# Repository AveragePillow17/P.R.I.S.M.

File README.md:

# P.R.I.S.M.
Portable Radio Instrument for Signal Monitoring

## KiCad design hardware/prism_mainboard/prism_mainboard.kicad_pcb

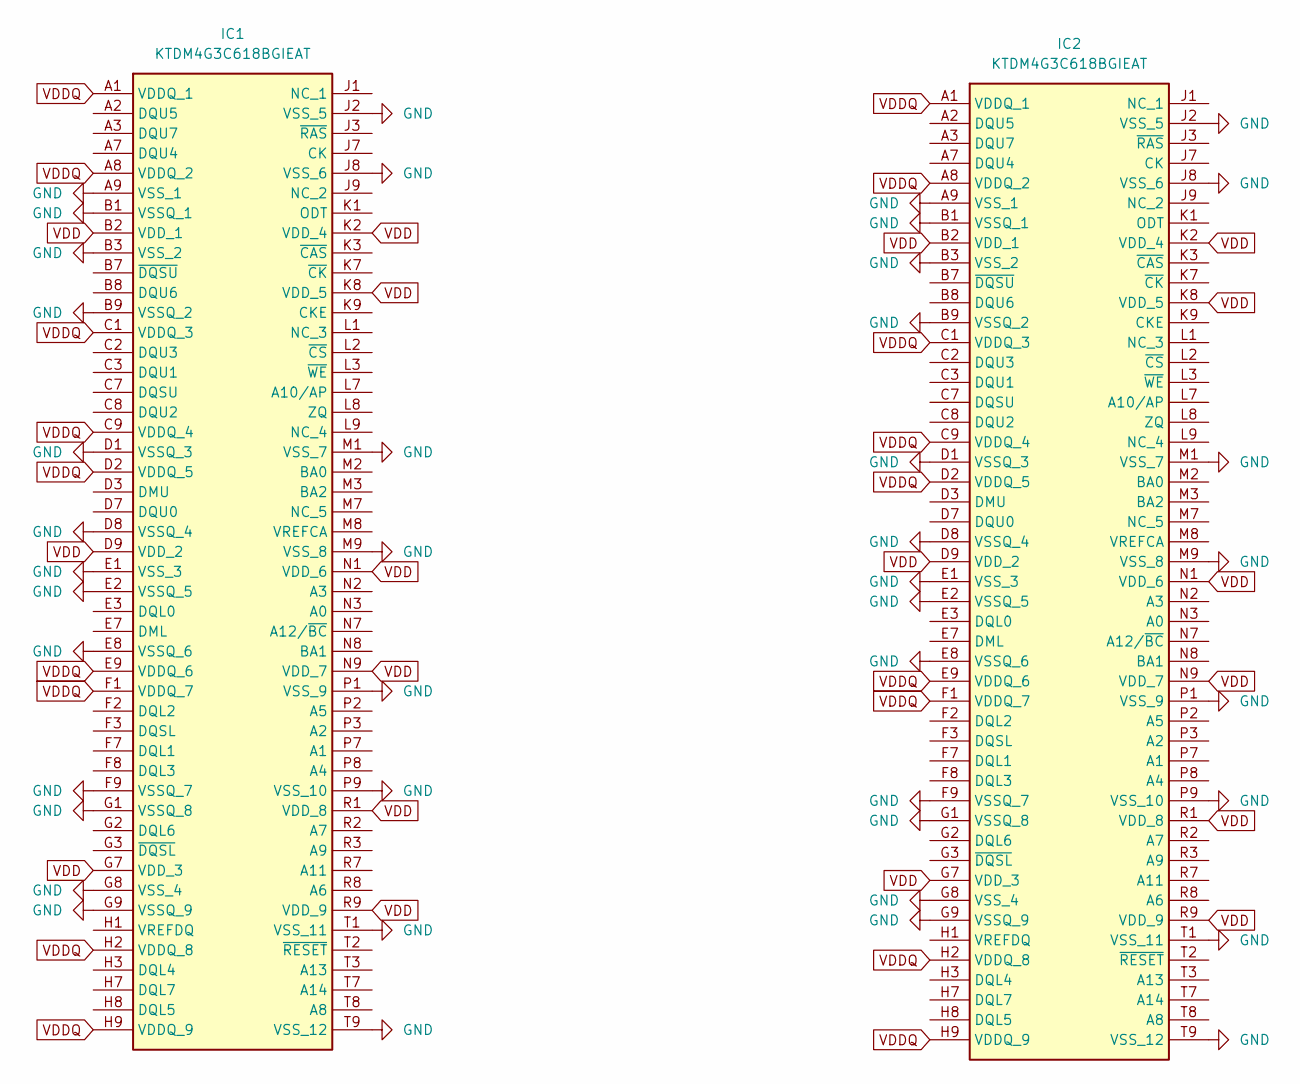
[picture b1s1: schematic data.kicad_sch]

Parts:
IC1, IC2: KTDM4G3C618BGIEAT; BGA96C80P9X16_750X1300X100; Mouser Part Number 473-M4G3C618BGIEAT

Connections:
A0: IC1.N3 (A0), IC2.N3 (A0); also elsewhere on the board
A1: IC1.P7 (A1), IC2.P7 (A1); also elsewhere on the board
A2: IC1.P3 (A2), IC2.P3 (A2); also elsewhere on the board
A3: IC1.N2 (A3), IC2.N2 (A3); also elsewhere on the board
A4: IC1.P8 (A4), IC2.P8 (A4); also elsewhere on the board
A5: IC1.P2 (A5), IC2.P2 (A5); also elsewhere on the board
A6: IC1.R8 (A6), IC2.R8 (A6); also elsewhere on the board
A7: IC1.R2 (A7), IC2.R2 (A7); also elsewhere on the board
A8: IC1.T8 (A8), IC2.T8 (A8); also elsewhere on the board
A9: IC1.R3 (A9), IC2.R3 (A9); also elsewhere on the board
A10: IC1.L7 (A10/AP), IC2.L7 (A10/AP); also elsewhere on the board
A11: IC1.R7 (A11), IC2.R7 (A11); also elsewhere on the board
A12: IC1.N7 (A12/~BC), IC2.N7 (A12/~BC); also elsewhere on the board
A13: IC1.T3 (A13), IC2.T3 (A13); also elsewhere on the board
A14: IC1.T7 (A14), IC2.T7 (A14); also elsewhere on the board
BA: IC1.M3 (BA2), IC2.M3 (BA2)
BA0: IC1.M2 (BA0), IC2.M2 (BA0); also elsewhere on the board
BA1: IC1.N8 (BA1), IC2.N8 (BA1); also elsewhere on the board
CAS: IC1.K3 (~CAS), IC2.K3 (~CAS); also elsewhere on the board
CKE: IC1.K9 (CKE), IC2.K9 (CKE); also elsewhere on the board
CKN: IC1.K7 (~CK), IC2.K7 (~CK); also elsewhere on the board
CKP: IC1.J7 (CK), IC2.J7 (CK); also elsewhere on the board
CS: IC1.L2 (~CS), IC2.L2 (~CS); also elsewhere on the board
DM0: IC1.E7 (DML); also elsewhere on the board
DM1: IC1.D3 (DMU)
DM2: IC2.E7 (DML); also elsewhere on the board
DM3: IC2.D3 (DMU)
DQL0_0: IC1.E3 (DQL0); also elsewhere on the board
DQL0_1: IC2.E3 (DQL0); also elsewhere on the board
DQL1_0: IC1.F7 (DQL1); also elsewhere on the board
DQL1_1: IC2.F7 (DQL1); also elsewhere on the board
DQL2_0: IC1.F2 (DQL2); also elsewhere on the board
DQL2_1: IC2.F2 (DQL2); also elsewhere on the board
DQL3_0: IC1.F8 (DQL3); also elsewhere on the board
DQL3_1: IC2.F8 (DQL3); also elsewhere on the board
DQL4_0: IC1.H3 (DQL4); also elsewhere on the board
DQL4_1: IC2.H3 (DQL4); also elsewhere on the board
DQL5_0: IC1.H8 (DQL5); also elsewhere on the board
DQL5_1: IC2.H8 (DQL5); also elsewhere on the board
DQL6_0: IC1.G2 (DQL6); also elsewhere on the board
DQL6_1: IC2.G2 (DQL6); also elsewhere on the board
DQL7_0: IC1.H7 (DQL7); also elsewhere on the board
DQL7_1: IC2.H7 (DQL7); also elsewhere on the board
DQSLN_0: IC1.G3 (~DQSL); also elsewhere on the board
DQSLN_1: IC2.G3 (~DQSL); also elsewhere on the board
DQSLP_0: IC1.F3 (DQSL); also elsewhere on the board
DQSLP_1: IC2.F3 (DQSL); also elsewhere on the board
DQSUN_0: IC1.B7 (~DQSU); also elsewhere on the board
DQSUN_1: IC2.B7 (~DQSU); also elsewhere on the board
DQSUP_0: IC1.C7 (DQSU); also elsewhere on the board
DQSUP_1: IC2.C7 (DQSU); also elsewhere on the board
DQU0_0: IC1.D7 (DQU0); also elsewhere on the board
DQU0_1: IC2.D7 (DQU0); also elsewhere on the board
DQU1_0: IC1.C3 (DQU1); also elsewhere on the board
DQU1_1: IC2.C3 (DQU1); also elsewhere on the board
DQU2_0: IC1.C8 (DQU2); also elsewhere on the board
DQU2_1: IC2.C8 (DQU2); also elsewhere on the board
DQU3_0: IC1.C2 (DQU3); also elsewhere on the board
DQU3_1: IC2.C2 (DQU3); also elsewhere on the board
DQU4_0: IC1.A7 (DQU4); also elsewhere on the board
DQU4_1: IC2.A7 (DQU4); also elsewhere on the board
DQU5_0: IC1.A2 (DQU5); also elsewhere on the board
DQU5_1: IC2.A2 (DQU5); also elsewhere on the board
DQU6_0: IC1.B8 (DQU6); also elsewhere on the board
DQU6_1: IC2.B8 (DQU6); also elsewhere on the board
DQU7_0: IC1.A3 (DQU7); also elsewhere on the board
DQU7_1: IC2.A3 (DQU7); also elsewhere on the board
GND: IC1.A9 (VSS_1), IC1.B1 (VSSQ_1), IC1.B3 (VSS_2), IC1.B9 (VSSQ_2), IC1.D1 (VSSQ_3), IC1.D8 (VSSQ_4), IC1.E1 (VSS_3), IC1.E2 (VSSQ_5), IC1.E8 (VSSQ_6), IC1.F9 (VSSQ_7), IC1.G1 (VSSQ_8), IC1.G8 (VSS_4), IC1.G9 (VSSQ_9), IC1.J2 (VSS_5), IC1.J8 (VSS_6), IC1.M1 (VSS_7), IC1.M9 (VSS_8), IC1.P1 (VSS_9), IC1.P9 (VSS_10), IC1.T1 (VSS_11), IC1.T9 (VSS_12), IC2.A9 (VSS_1), IC2.B1 (VSSQ_1), IC2.B3 (VSS_2), IC2.B9 (VSSQ_2), IC2.D1 (VSSQ_3), IC2.D8 (VSSQ_4), IC2.E1 (VSS_3), IC2.E2 (VSSQ_5), IC2.E8 (VSSQ_6), IC2.F9 (VSSQ_7), IC2.G1 (VSSQ_8), IC2.G8 (VSS_4), IC2.G9 (VSSQ_9), IC2.J2 (VSS_5), IC2.J8 (VSS_6), IC2.M1 (VSS_7), IC2.M9 (VSS_8), IC2.P1 (VSS_9), IC2.P9 (VSS_10), IC2.T1 (VSS_11), IC2.T9 (VSS_12); also elsewhere on the board
ODT: IC1.K1 (ODT), IC2.K1 (ODT); also elsewhere on the board
RAS: IC1.J3 (~RAS), IC2.J3 (~RAS); also elsewhere on the board
VCCO_DDR: IC1.A1 (VDDQ_1), IC1.A8 (VDDQ_2), IC1.B2 (VDD_1), IC1.C1 (VDDQ_3), IC1.C9 (VDDQ_4), IC1.D2 (VDDQ_5), IC1.D9 (VDD_2), IC1.E9 (VDDQ_6), IC1.F1 (VDDQ_7), IC1.G7 (VDD_3), IC1.H2 (VDDQ_8), IC1.H9 (VDDQ_9), IC1.K2 (VDD_4), IC1.K8 (VDD_5), IC1.N1 (VDD_6), IC1.N9 (VDD_7), IC1.R1 (VDD_8), IC1.R9 (VDD_9), IC2.A1 (VDDQ_1), IC2.A8 (VDDQ_2), IC2.B2 (VDD_1), IC2.C1 (VDDQ_3), IC2.C9 (VDDQ_4), IC2.D2 (VDDQ_5), IC2.D9 (VDD_2), IC2.E9 (VDDQ_6), IC2.F1 (VDDQ_7), IC2.G7 (VDD_3), IC2.H2 (VDDQ_8), IC2.H9 (VDDQ_9), IC2.K2 (VDD_4), IC2.K8 (VDD_5), IC2.N1 (VDD_6), IC2.N9 (VDD_7), IC2.R1 (VDD_8), IC2.R9 (VDD_9); also elsewhere on the board
WE: IC1.L3 (~WE), IC2.L3 (~WE); also elsewhere on the board

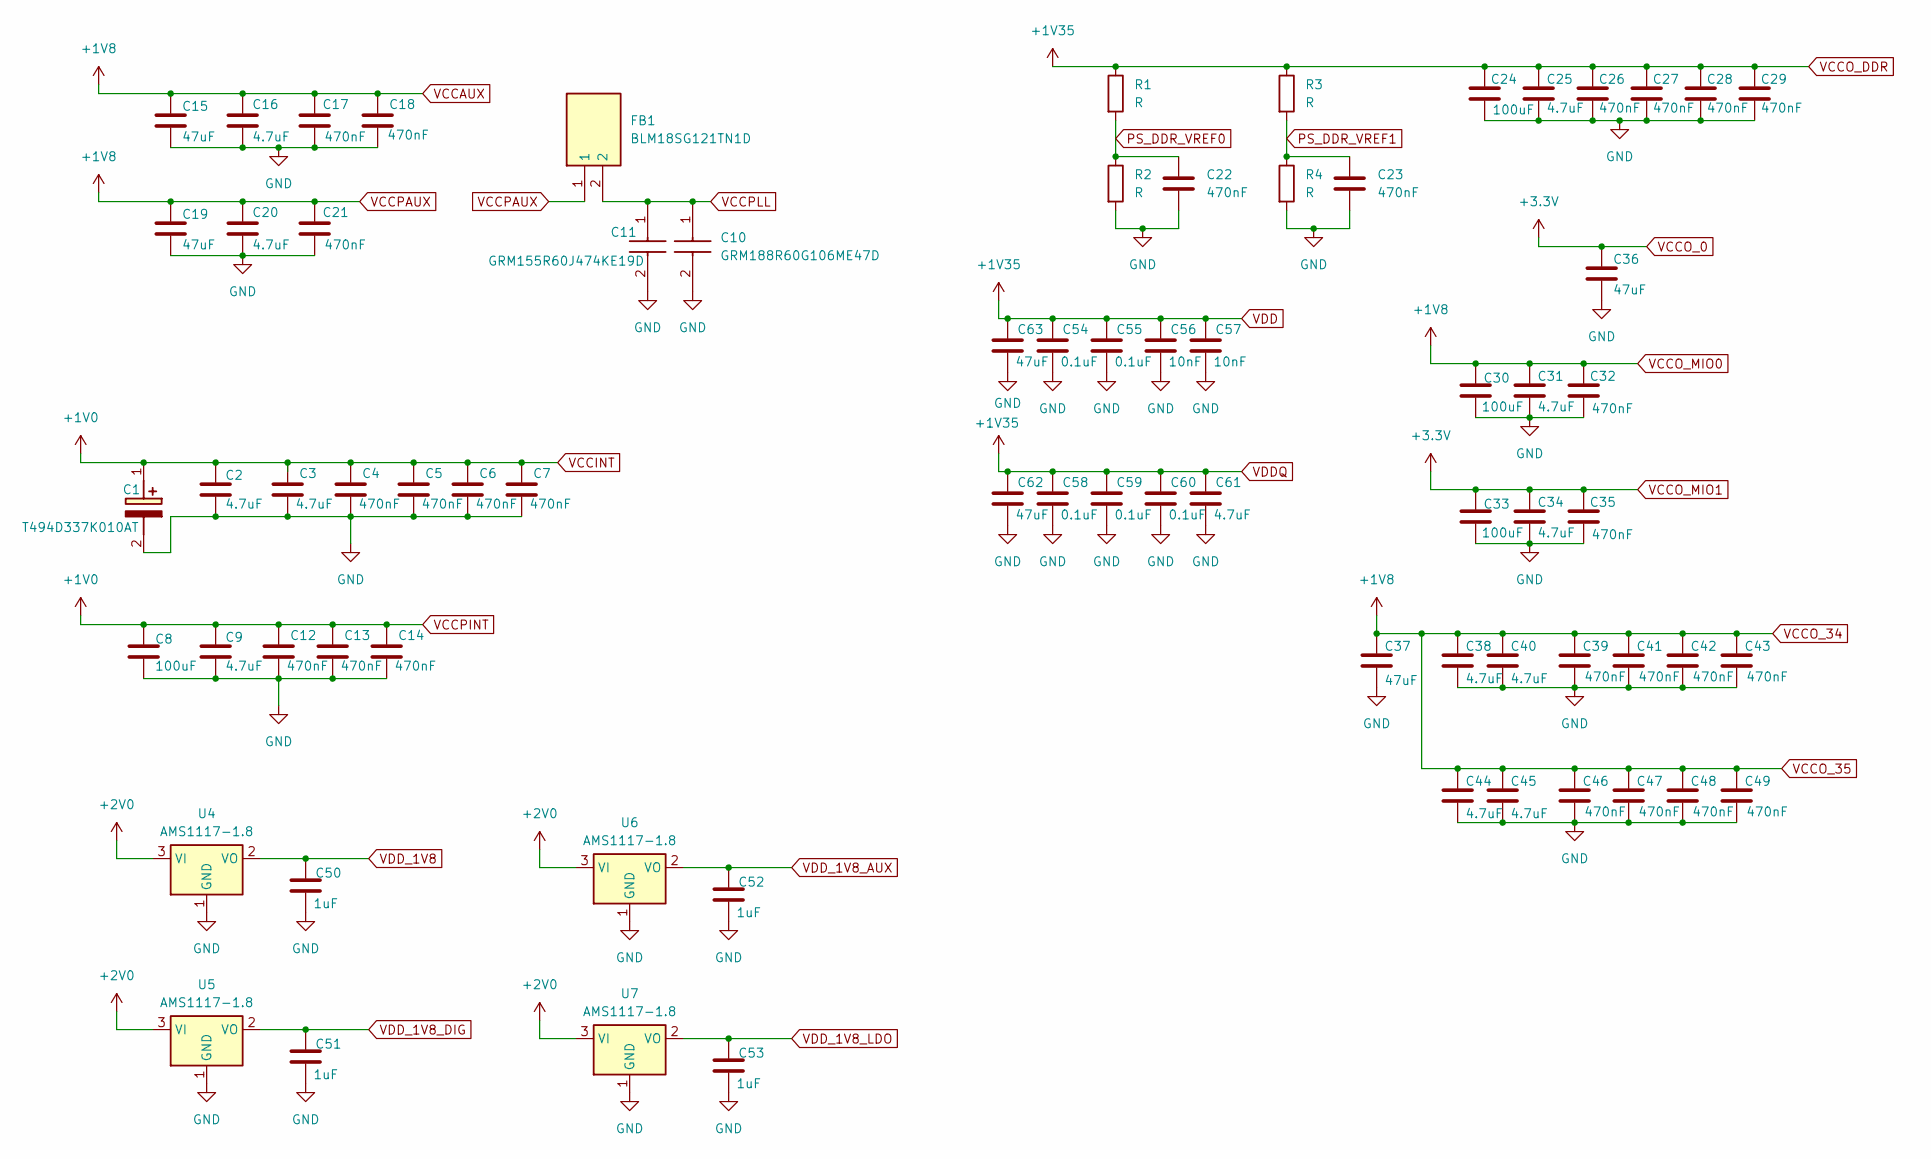
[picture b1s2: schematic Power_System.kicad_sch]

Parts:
C1: T494D337K010AT; T494D; Manufacturer_Part_Number T494D337K010AT; Mouser Part Number 80-T494D337K010AT
C2, C3, C9, C16, C20, C25, C31, C34, C38, C40, C44, C45: 4.7uF; C_0805_2012Metric_Pad1.18x1.45mm_HandSolder
C4, C5, C6, C7, C12, C13, C14, C17, C18, C21, C22, C23, C26, C27, C28, C29, C32, C35, C39, C41, C42, C43, C46, C47, C48, C49: 470nF; C_0402_1005Metric_Pad0.74x0.62mm_HandSolder
C8, C24, C30, C33: 100uF; C_0805_2012Metric_Pad1.18x1.45mm_HandSolder
C10: GRM188R60G106ME47D; CAPC1608X90N; Mouser Part Number 81-GRM188R60G106ME47
C11: GRM155R60J474KE19D; CAPC1005X70N; Mouser Part Number 81-GRM155R60J474KE9D
C15, C19, C36, C37, C62, C63: 47uF; C_0805_2012Metric_Pad1.18x1.45mm_HandSolder
C50, C51, C52, C53: 1uF; C_0805_2012Metric_Pad1.18x1.45mm_HandSolder
C54, C55, C58, C59, C60: 0.1uF; C_0402_1005Metric
C56: 10nF; C_0402_1005Metric
C57: 10nF; C_0402_1005Metric_Pad0.74x0.62mm_HandSolder
C61: 4.7uF; C_0402_1005Metric_Pad0.74x0.62mm_HandSolder
FB1: BLM18SG121TN1D; BLM18EG101TH1D; Mouser Part Number 81-BLM18SG121TN1D
R1, R2, R3, R4: R; R_0805_2012Metric_Pad1.20x1.40mm_HandSolder
U4, U5, U6, U7: AMS1117-1.8; SOT-223-3_TabPin2

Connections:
+2V0: U4.3 (VI), U5.3 (VI), U6.3 (VI), U7.3 (VI)
GND: C1.2 (-), C2.2, C3.2, C4.2, C5.2, C6.2, C7.2, C8.2, C9.2, C10.2, C11.2, C12.2, C13.2, C14.2, C15.2, C16.2, C17.2, C18.2, C19.2, C20.2, C21.2, C22.2, C23.2, C24.2, C25.2, C26.2, C27.2, C28.2, C29.2, C30.2, C31.2, C32.2, C33.2, C34.2, C35.2, C36.2, C37.2, C38.2, C39.2, C40.2, C41.2, C42.2, C43.2, C44.2, C45.2, C46.2, C47.2, C48.2, C49.2, C50.2, C51.2, C52.2, C53.2, C54.2, C55.2, C56.2, C57.2, C58.2, C59.2, C60.2, C61.2, C62.2, C63.2, R2.2, R4.2, U4.1 (GND), U5.1 (GND), U6.1 (GND), U7.1 (GND); also elsewhere on the board
PS_DDR_VREF0: C22.1, R1.2, R2.1
PS_DDR_VREF1: C23.1, R3.2, R4.1
VCCAUX: C15.1, C16.1, C17.1, C18.1, C19.1, C20.1, C21.1, C30.1, C31.1, C32.1, C37.1, C38.1, C39.1, C40.1, C41.1, C42.1, C43.1, C44.1, C45.1, C46.1, C47.1, C48.1, C49.1, FB1.1; also elsewhere on the board
VCCINT: C1.1 (+), C2.1, C3.1, C4.1, C5.1, C6.1, C7.1, C8.1, C9.1, C12.1, C13.1, C14.1; also elsewhere on the board
VCCO_0: C33.1, C34.1, C35.1, C36.1; also elsewhere on the board
VCCO_DDR: C24.1, C25.1, C26.1, C27.1, C28.1, C29.1, C54.1, C55.1, C56.1, C57.1, C58.1, C59.1, C60.1, C61.1, C62.1, C63.1, R1.1, R3.1; also elsewhere on the board
VCCPLL: C10.1, C11.1, FB1.2
VDD_1V8: C50.1, U4.2 (VO); also elsewhere on the board
VDD_1V8_AUX: C52.1, U6.2 (VO)
VDD_1V8_DIG: C51.1, U5.2 (VO); also elsewhere on the board
VDD_1V8_LDO: C53.1, U7.2 (VO); also elsewhere on the board

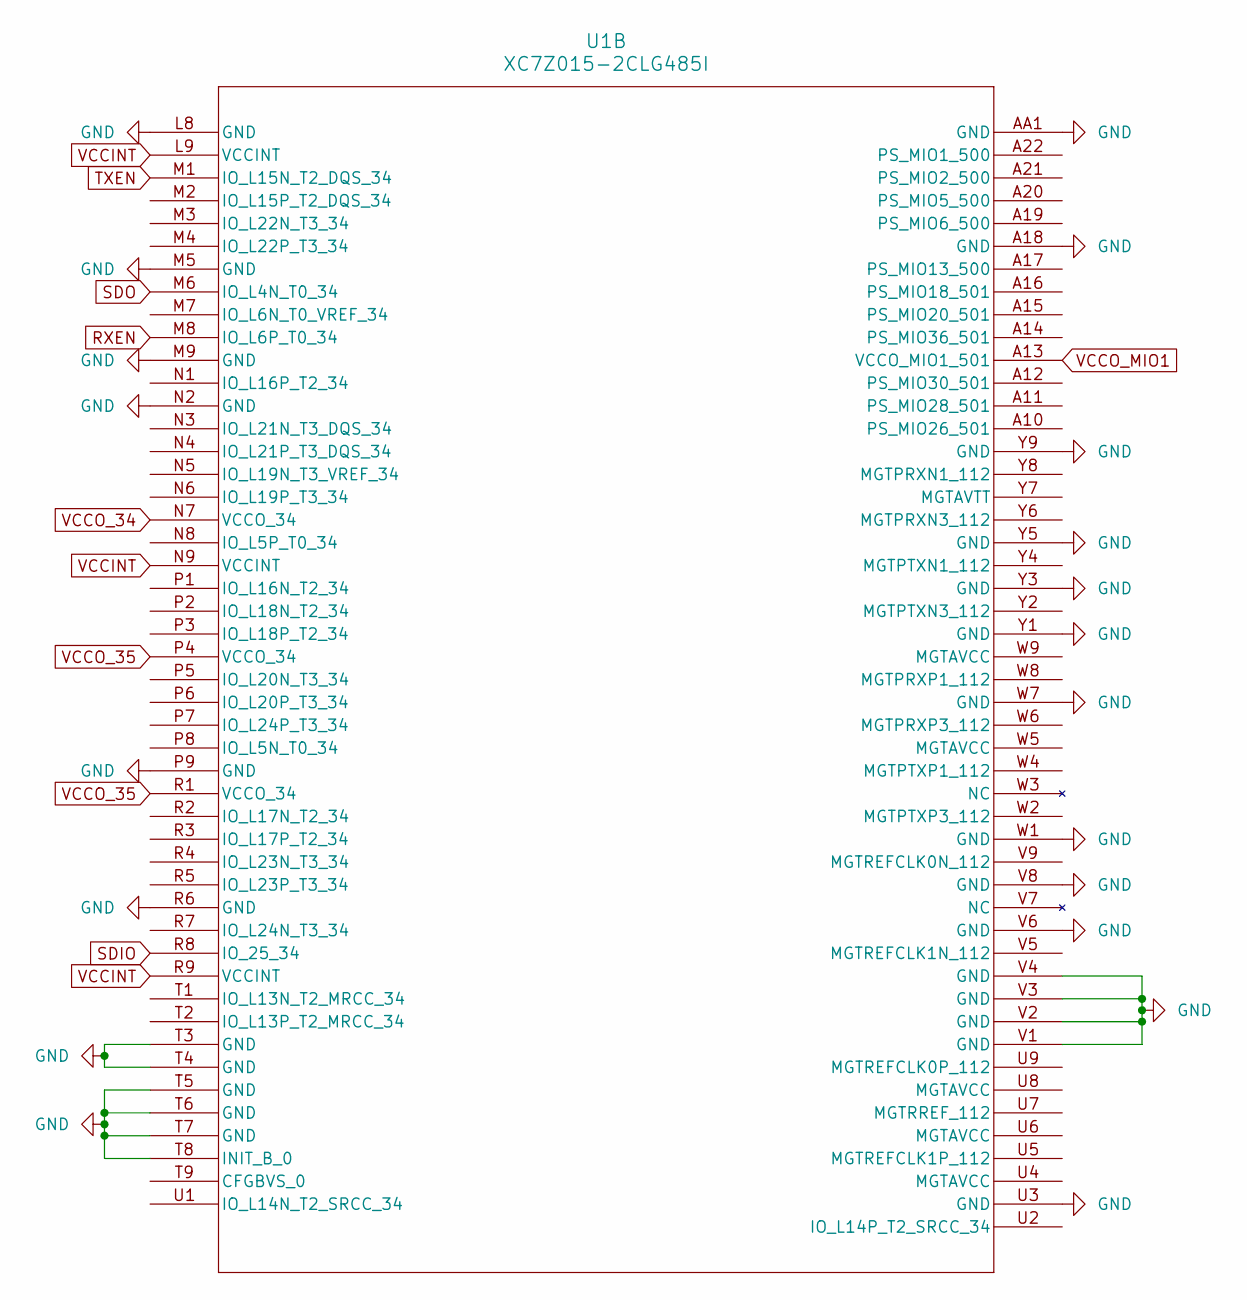
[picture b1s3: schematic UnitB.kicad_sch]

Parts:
U1: XC7Z015-2CLG485I; CLG485_XIL

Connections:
CKE: U1.T19 (PS_DDR_CKE_502); also elsewhere on the board
CLKOUT: U1.A14 (PS_MIO36_501); also elsewhere on the board
DQL1_1: U1.T20 (PS_DDR_DQ17_502); also elsewhere on the board
DQL3_1: U1.T22 (PS_DDR_DQ19_502); also elsewhere on the board
DQL4_1: U1.R20 (PS_DDR_DQ20_502); also elsewhere on the board
DQL5_1: U1.T21 (PS_DDR_DQ21_502); also elsewhere on the board
DQL7_1: U1.R22 (PS_DDR_DQ23_502); also elsewhere on the board
DQSUN_1: U1.W21 (PS_DDR_DQS_N3_502); also elsewhere on the board
DQSUP_1: U1.V21 (PS_DDR_DQS_P3_502); also elsewhere on the board
DQU0_1: U1.Y20 (PS_DDR_DQ24_502); also elsewhere on the board
DQU1_1: U1.U22 (PS_DDR_DQ25_502); also elsewhere on the board
DQU2_1: U1.AA22 (PS_DDR_DQ26_502); also elsewhere on the board
DQU3_1: U1.U21 (PS_DDR_DQ27_502); also elsewhere on the board
DQU4_1: U1.W22 (PS_DDR_DQ28_502); also elsewhere on the board
DQU5_1: U1.W20 (PS_DDR_DQ29_502); also elsewhere on the board
DQU6_1: U1.V20 (PS_DDR_DQ30_502); also elsewhere on the board
DQU7_1: U1.Y22 (PS_DDR_DQ31_502); also elsewhere on the board
GND: U1.A18 (GND), U1.AA1 (GND), U1.AA10 (GND), U1.AA18 (GND), U1.AB10 (GND), U1.AB15 (GND), U1.L8 (GND), U1.M5 (GND), U1.M9 (GND), U1.N2 (GND), U1.P9 (GND), U1.R6 (GND), U1.T3 (GND), U1.T4 (GND), U1.T5 (GND), U1.T6 (GND), U1.T7 (GND), U1.T8 (INIT_B_0), U1.T13 (GND), U1.U3 (GND), U1.U10 (GND), U1.U20 (GND), U1.V1 (GND), U1.V2 (GND), U1.V3 (GND), U1.V4 (GND), U1.V6 (GND), U1.V8 (GND), U1.V17 (GND), U1.W1 (GND), U1.W7 (GND), U1.W10 (GND), U1.W14 (GND), U1.Y1 (GND), U1.Y3 (GND), U1.Y5 (GND), U1.Y9 (GND), U1.Y10 (GND), U1.Y11 (GND), U1.Y21 (GND); also elsewhere on the board
LM_RST: U1.N8 (IO_L5P_T0_34); also elsewhere on the board
RAS: U1.R18 (PS_DDR_RAS_B_502); also elsewhere on the board
RXEN: U1.M8 (IO_L6P_T0_34); also elsewhere on the board
SDIO: U1.R8 (IO_25_34); also elsewhere on the board
SDO: U1.M6 (IO_L4N_T0_34); also elsewhere on the board
STP: U1.A12 (PS_MIO30_501); also elsewhere on the board
TXEN: U1.M1 (IO_L15N_T2_DQS_34); also elsewhere on the board
USB_D4: U1.A11 (PS_MIO28_501); also elsewhere on the board
VCCAUX: U1.N7 (VCCO_34), U1.P4 (VCCO_34), U1.R1 (VCCO_34), U1.T12 (VCCAUX); also elsewhere on the board
VCCINT: U1.L9 (VCCINT), U1.N9 (VCCINT), U1.R9 (VCCINT); also elsewhere on the board
VCCO_0: U1.A13 (VCCO_MIO1_501); also elsewhere on the board
VCCO_DDR: U1.R21 (VCCO_DDR_502), U1.V22 (VCCO_DDR_502); also elsewhere on the board
WE: U1.R19 (PS_DDR_WE_B_502); also elsewhere on the board

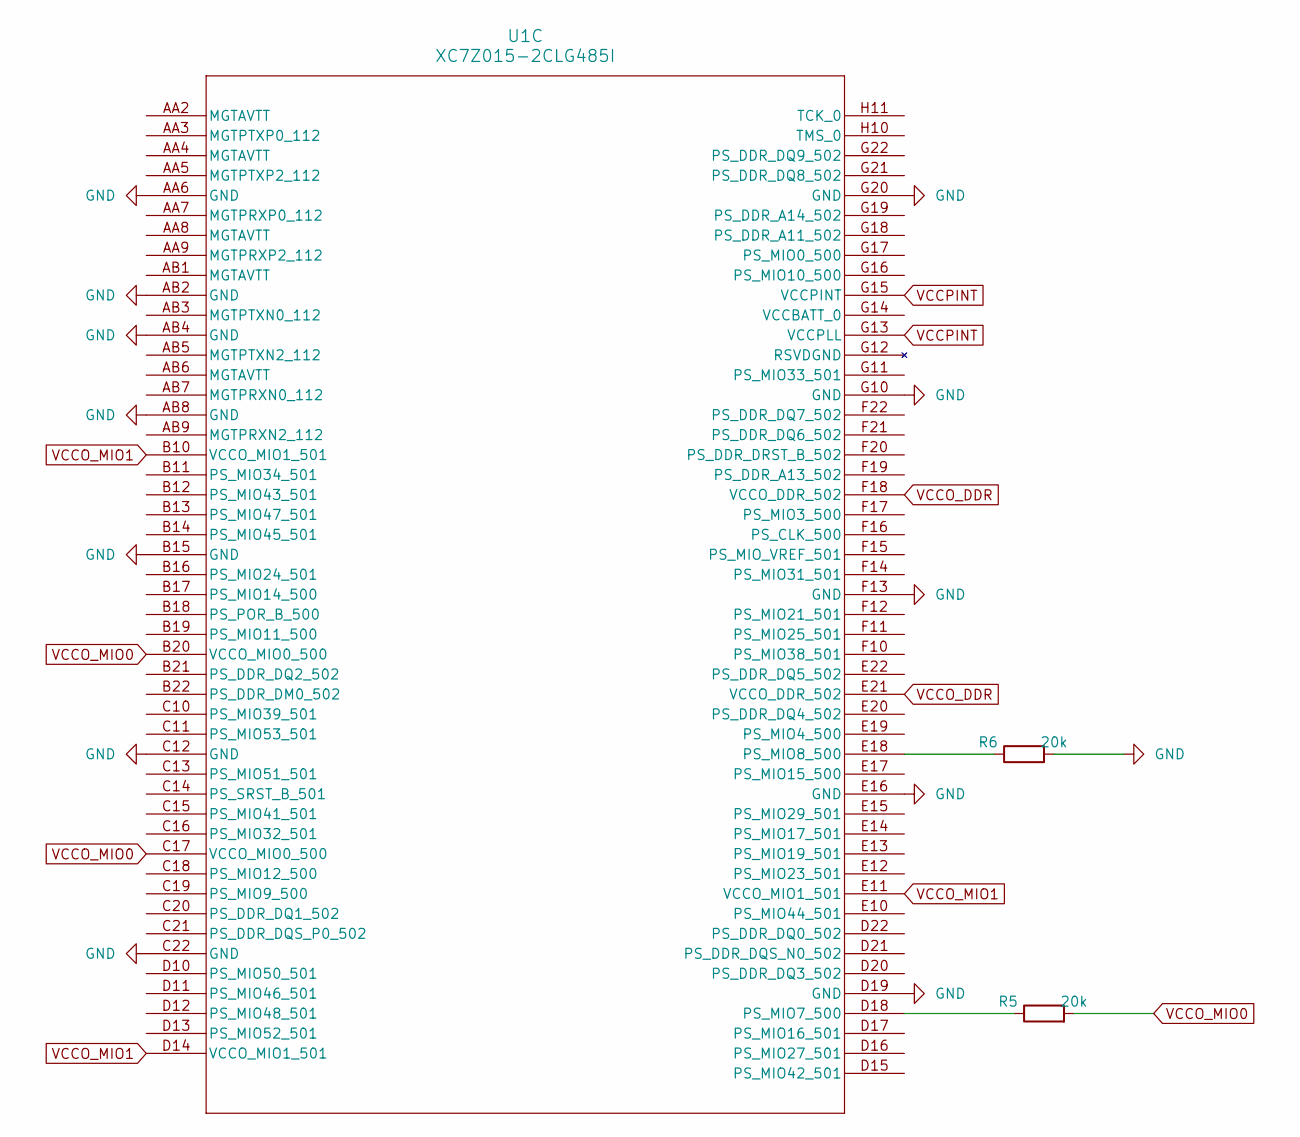
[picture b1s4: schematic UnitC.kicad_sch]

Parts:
R5, R6: 20k; C_0805_2012Metric_Pad1.18x1.45mm_HandSolder
U1: XC7Z015-2CLG485I; CLG485_XIL

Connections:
A11: U1.G18 (PS_DDR_A11_502); also elsewhere on the board
A13: U1.F19 (PS_DDR_A13_502); also elsewhere on the board
A14: U1.G19 (PS_DDR_A14_502); also elsewhere on the board
CKE: U1.T19 (PS_DDR_CKE_502); also elsewhere on the board
CLK: U1.F16 (PS_CLK_500)
DIR: U1.E15 (PS_MIO29_501); also elsewhere on the board
DM0: U1.B22 (PS_DDR_DM0_502); also elsewhere on the board
DQL0_0: U1.D22 (PS_DDR_DQ0_502); also elsewhere on the board
DQL1_0: U1.C20 (PS_DDR_DQ1_502); also elsewhere on the board
DQL1_1: U1.T20 (PS_DDR_DQ17_502); also elsewhere on the board
DQL2_0: U1.B21 (PS_DDR_DQ2_502); also elsewhere on the board
DQL3_0: U1.D20 (PS_DDR_DQ3_502); also elsewhere on the board
DQL3_1: U1.T22 (PS_DDR_DQ19_502); also elsewhere on the board
DQL4_0: U1.E20 (PS_DDR_DQ4_502); also elsewhere on the board
DQL4_1: U1.R20 (PS_DDR_DQ20_502); also elsewhere on the board
DQL5_0: U1.E22 (PS_DDR_DQ5_502); also elsewhere on the board
DQL5_1: U1.T21 (PS_DDR_DQ21_502); also elsewhere on the board
DQL6_0: U1.F21 (PS_DDR_DQ6_502); also elsewhere on the board
DQL7_0: U1.F22 (PS_DDR_DQ7_502); also elsewhere on the board
DQL7_1: U1.R22 (PS_DDR_DQ23_502); also elsewhere on the board
DQSLN_0: U1.D21 (PS_DDR_DQS_N0_502); also elsewhere on the board
DQSLP_0: U1.C21 (PS_DDR_DQS_P0_502); also elsewhere on the board
DQSUN_1: U1.W21 (PS_DDR_DQS_N3_502); also elsewhere on the board
DQSUP_1: U1.V21 (PS_DDR_DQS_P3_502); also elsewhere on the board
DQU0_0: U1.G21 (PS_DDR_DQ8_502); also elsewhere on the board
DQU0_1: U1.Y20 (PS_DDR_DQ24_502); also elsewhere on the board
DQU1_0: U1.G22 (PS_DDR_DQ9_502); also elsewhere on the board
DQU1_1: U1.U22 (PS_DDR_DQ25_502); also elsewhere on the board
DQU2_1: U1.AA22 (PS_DDR_DQ26_502); also elsewhere on the board
DQU3_1: U1.U21 (PS_DDR_DQ27_502); also elsewhere on the board
DQU4_1: U1.W22 (PS_DDR_DQ28_502); also elsewhere on the board
DQU5_1: U1.W20 (PS_DDR_DQ29_502); also elsewhere on the board
DQU6_1: U1.V20 (PS_DDR_DQ30_502); also elsewhere on the board
DQU7_1: U1.Y22 (PS_DDR_DQ31_502); also elsewhere on the board
GND: R6.2, U1.AA6 (GND), U1.AA10 (GND), U1.AA18 (GND), U1.AB2 (GND), U1.AB4 (GND), U1.AB8 (GND), U1.AB10 (GND), U1.AB15 (GND), U1.B15 (GND), U1.C12 (GND), U1.C22 (GND), U1.D19 (GND), U1.E16 (GND), U1.F13 (GND), U1.G10 (GND), U1.G20 (GND), U1.T13 (GND), U1.U10 (GND), U1.U20 (GND), U1.V17 (GND), U1.W10 (GND), U1.W14 (GND), U1.Y10 (GND), U1.Y11 (GND), U1.Y21 (GND); also elsewhere on the board
NXT: U1.F14 (PS_MIO31_501); also elsewhere on the board
unnamed: R5.1, U1.D18 (PS_MIO7_500)
unnamed: R6.1, U1.E18 (PS_MIO8_500)
RAS: U1.R18 (PS_DDR_RAS_B_502); also elsewhere on the board
SD_CMD: U1.C15 (PS_MIO41_501); also elsewhere on the board
SD_D0: U1.D15 (PS_MIO42_501); also elsewhere on the board
SD_D1: U1.B12 (PS_MIO43_501); also elsewhere on the board
SD_D2: U1.E10 (PS_MIO44_501); also elsewhere on the board
SD_D3: U1.B14 (PS_MIO45_501); also elsewhere on the board
USB_D0: U1.C16 (PS_MIO32_501); also elsewhere on the board
USB_D2: U1.G11 (PS_MIO33_501); also elsewhere on the board
USB_D3: U1.B11 (PS_MIO34_501); also elsewhere on the board
USB_D6: U1.F10 (PS_MIO38_501); also elsewhere on the board
USB_D7: U1.C10 (PS_MIO39_501); also elsewhere on the board
VCCAUX: R5.2, U1.B20 (VCCO_MIO0_500), U1.C17 (VCCO_MIO0_500), U1.T12 (VCCAUX); also elsewhere on the board
VCCINT: U1.G13 (VCCPLL), U1.G15 (VCCPINT); also elsewhere on the board
VCCO_0: U1.B10 (VCCO_MIO1_501), U1.D14 (VCCO_MIO1_501), U1.E11 (VCCO_MIO1_501); also elsewhere on the board
VCCO_DDR: U1.E21 (VCCO_DDR_502), U1.F18 (VCCO_DDR_502), U1.R21 (VCCO_DDR_502), U1.V22 (VCCO_DDR_502); also elsewhere on the board
WE: U1.R19 (PS_DDR_WE_B_502); also elsewhere on the board

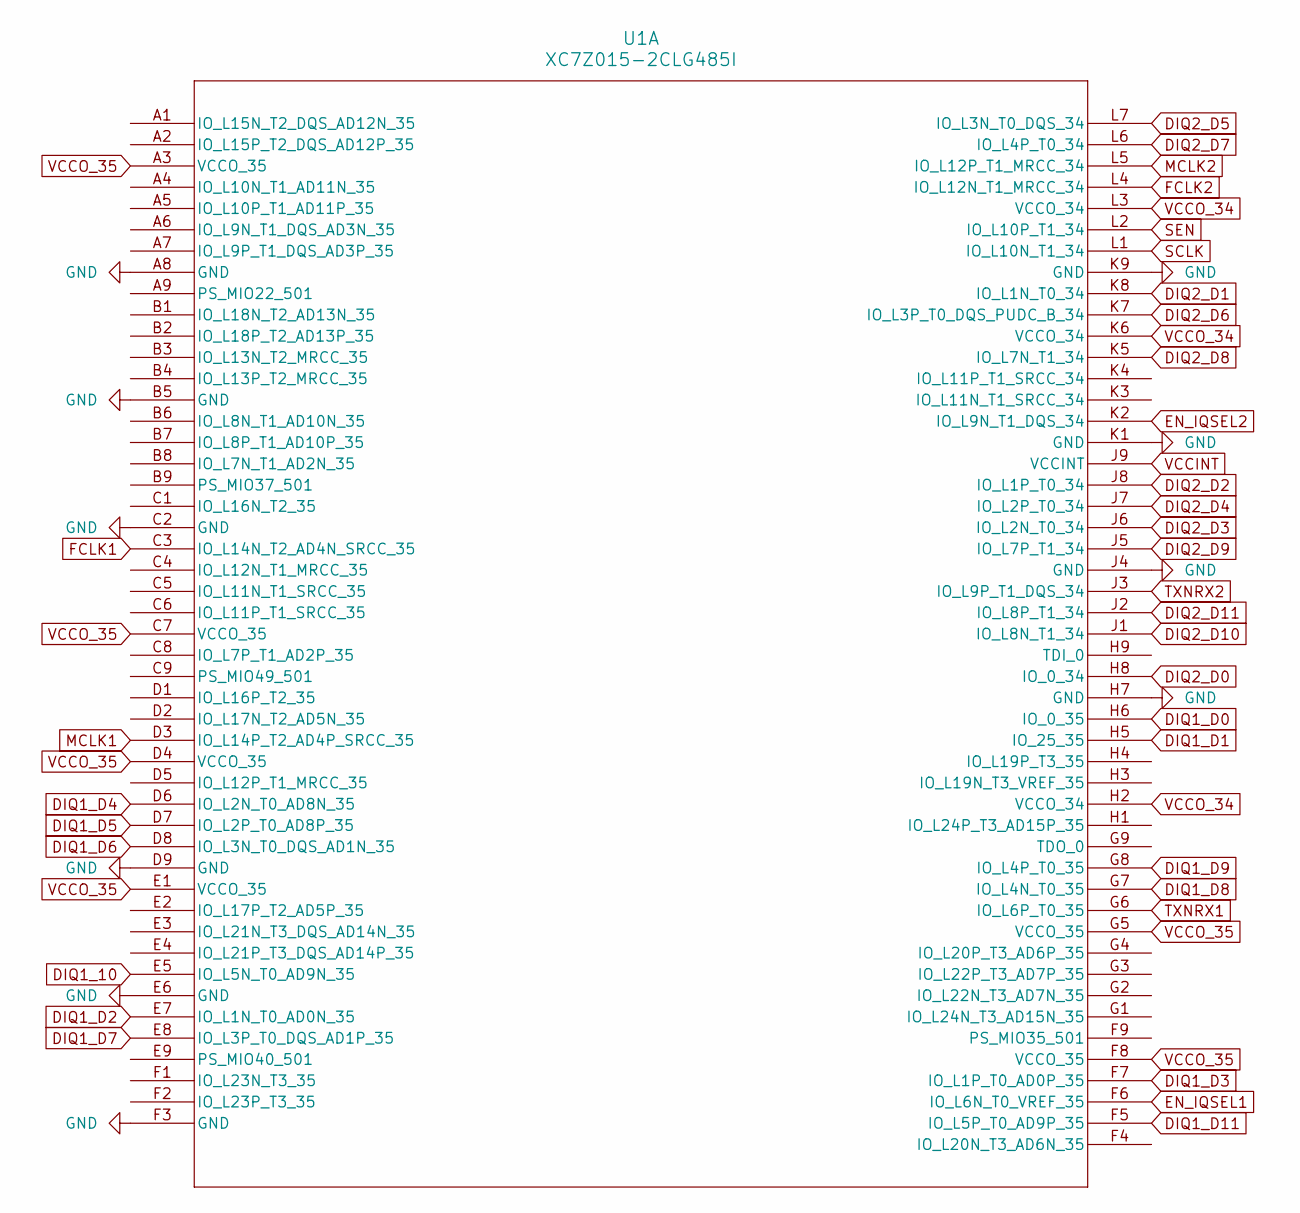
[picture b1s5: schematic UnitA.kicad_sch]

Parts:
U1: XC7Z015-2CLG485I; CLG485_XIL

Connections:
CKE: U1.T19 (PS_DDR_CKE_502); also elsewhere on the board
DIQ1_D0: U1.H6 (IO_0_35); also elsewhere on the board
DIQ1_D1: U1.H5 (IO_25_35); also elsewhere on the board
DIQ1_D2: U1.E7 (IO_L1N_T0_AD0N_35); also elsewhere on the board
DIQ1_D3: U1.F7 (IO_L1P_T0_AD0P_35); also elsewhere on the board
DIQ1_D4: U1.D6 (IO_L2N_T0_AD8N_35); also elsewhere on the board
DIQ1_D5: U1.D7 (IO_L2P_T0_AD8P_35); also elsewhere on the board
DIQ1_D6: U1.D8 (IO_L3N_T0_DQS_AD1N_35); also elsewhere on the board
DIQ1_D7: U1.E8 (IO_L3P_T0_DQS_AD1P_35); also elsewhere on the board
DIQ1_D8: U1.G7 (IO_L4N_T0_35); also elsewhere on the board
DIQ1_D9: U1.G8 (IO_L4P_T0_35); also elsewhere on the board
DIQ1_D11: U1.F5 (IO_L5P_T0_AD9P_35); also elsewhere on the board
DIQ2_D0: U1.H8 (IO_0_34); also elsewhere on the board
DIQ2_D1: U1.K8 (IO_L1N_T0_34); also elsewhere on the board
DIQ2_D2: U1.J8 (IO_L1P_T0_34); also elsewhere on the board
DIQ2_D3: U1.J6 (IO_L2N_T0_34); also elsewhere on the board
DIQ2_D4: U1.J7 (IO_L2P_T0_34); also elsewhere on the board
DIQ2_D5: U1.L7 (IO_L3N_T0_DQS_34); also elsewhere on the board
DIQ2_D6: U1.K7 (IO_L3P_T0_DQS_PUDC_B_34); also elsewhere on the board
DIQ2_D7: U1.L6 (IO_L4P_T0_34); also elsewhere on the board
DIQ2_D8: U1.K5 (IO_L7N_T1_34); also elsewhere on the board
DIQ2_D9: U1.J5 (IO_L7P_T1_34); also elsewhere on the board
DIQ2_D10: U1.J1 (IO_L8N_T1_34); also elsewhere on the board
DIQ2_D11: U1.J2 (IO_L8P_T1_34); also elsewhere on the board
DQL1_1: U1.T20 (PS_DDR_DQ17_502); also elsewhere on the board
DQL3_1: U1.T22 (PS_DDR_DQ19_502); also elsewhere on the board
DQL4_1: U1.R20 (PS_DDR_DQ20_502); also elsewhere on the board
DQL5_1: U1.T21 (PS_DDR_DQ21_502); also elsewhere on the board
DQL7_1: U1.R22 (PS_DDR_DQ23_502); also elsewhere on the board
DQSUN_1: U1.W21 (PS_DDR_DQS_N3_502); also elsewhere on the board
DQSUP_1: U1.V21 (PS_DDR_DQS_P3_502); also elsewhere on the board
DQU0_1: U1.Y20 (PS_DDR_DQ24_502); also elsewhere on the board
DQU1_1: U1.U22 (PS_DDR_DQ25_502); also elsewhere on the board
DQU2_1: U1.AA22 (PS_DDR_DQ26_502); also elsewhere on the board
DQU3_1: U1.U21 (PS_DDR_DQ27_502); also elsewhere on the board
DQU4_1: U1.W22 (PS_DDR_DQ28_502); also elsewhere on the board
DQU5_1: U1.W20 (PS_DDR_DQ29_502); also elsewhere on the board
DQU6_1: U1.V20 (PS_DDR_DQ30_502); also elsewhere on the board
DQU7_1: U1.Y22 (PS_DDR_DQ31_502); also elsewhere on the board
EN_IQSEL1: U1.F6 (IO_L6N_T0_VREF_35); also elsewhere on the board
EN_IQSEL2: U1.K2 (IO_L9N_T1_DQS_34); also elsewhere on the board
FCLK1: U1.C3 (IO_L14N_T2_AD4N_SRCC_35); also elsewhere on the board
FCLK2: U1.L4 (IO_L12N_T1_MRCC_34); also elsewhere on the board
GND: U1.A8 (GND), U1.AA10 (GND), U1.AA18 (GND), U1.AB10 (GND), U1.AB15 (GND), U1.B5 (GND), U1.C2 (GND), U1.D9 (GND), U1.E6 (GND), U1.F3 (GND), U1.H7 (GND), U1.J4 (GND), U1.K1 (GND), U1.K9 (GND), U1.T13 (GND), U1.U10 (GND), U1.U20 (GND), U1.V17 (GND), U1.W10 (GND), U1.W14 (GND), U1.Y10 (GND), U1.Y11 (GND), U1.Y21 (GND); also elsewhere on the board
MCLK1: U1.D3 (IO_L14P_T2_AD4P_SRCC_35); also elsewhere on the board
MCLK2: U1.L5 (IO_L12P_T1_MRCC_34); also elsewhere on the board
RAS: U1.R18 (PS_DDR_RAS_B_502); also elsewhere on the board
SCLK: U1.L1 (IO_L10N_T1_34); also elsewhere on the board
SD_CLK: U1.E9 (PS_MIO40_501); also elsewhere on the board
SEN: U1.L2 (IO_L10P_T1_34); also elsewhere on the board
TXNRX1: U1.G6 (IO_L6P_T0_35); also elsewhere on the board
TXNRX2: U1.J3 (IO_L9P_T1_DQS_34); also elsewhere on the board
USB_D3: U1.F9 (PS_MIO35_501); also elsewhere on the board
USB_D5: U1.B9 (PS_MIO37_501); also elsewhere on the board
VCCAUX: U1.A3 (VCCO_35), U1.C7 (VCCO_35), U1.D4 (VCCO_35), U1.E1 (VCCO_35), U1.F8 (VCCO_35), U1.G5 (VCCO_35), U1.H2 (VCCO_34), U1.K6 (VCCO_34), U1.L3 (VCCO_34), U1.T12 (VCCAUX); also elsewhere on the board
VCCINT: U1.J9 (VCCINT); also elsewhere on the board
VCCO_DDR: U1.R21 (VCCO_DDR_502), U1.V22 (VCCO_DDR_502); also elsewhere on the board
WE: U1.R19 (PS_DDR_WE_B_502); also elsewhere on the board

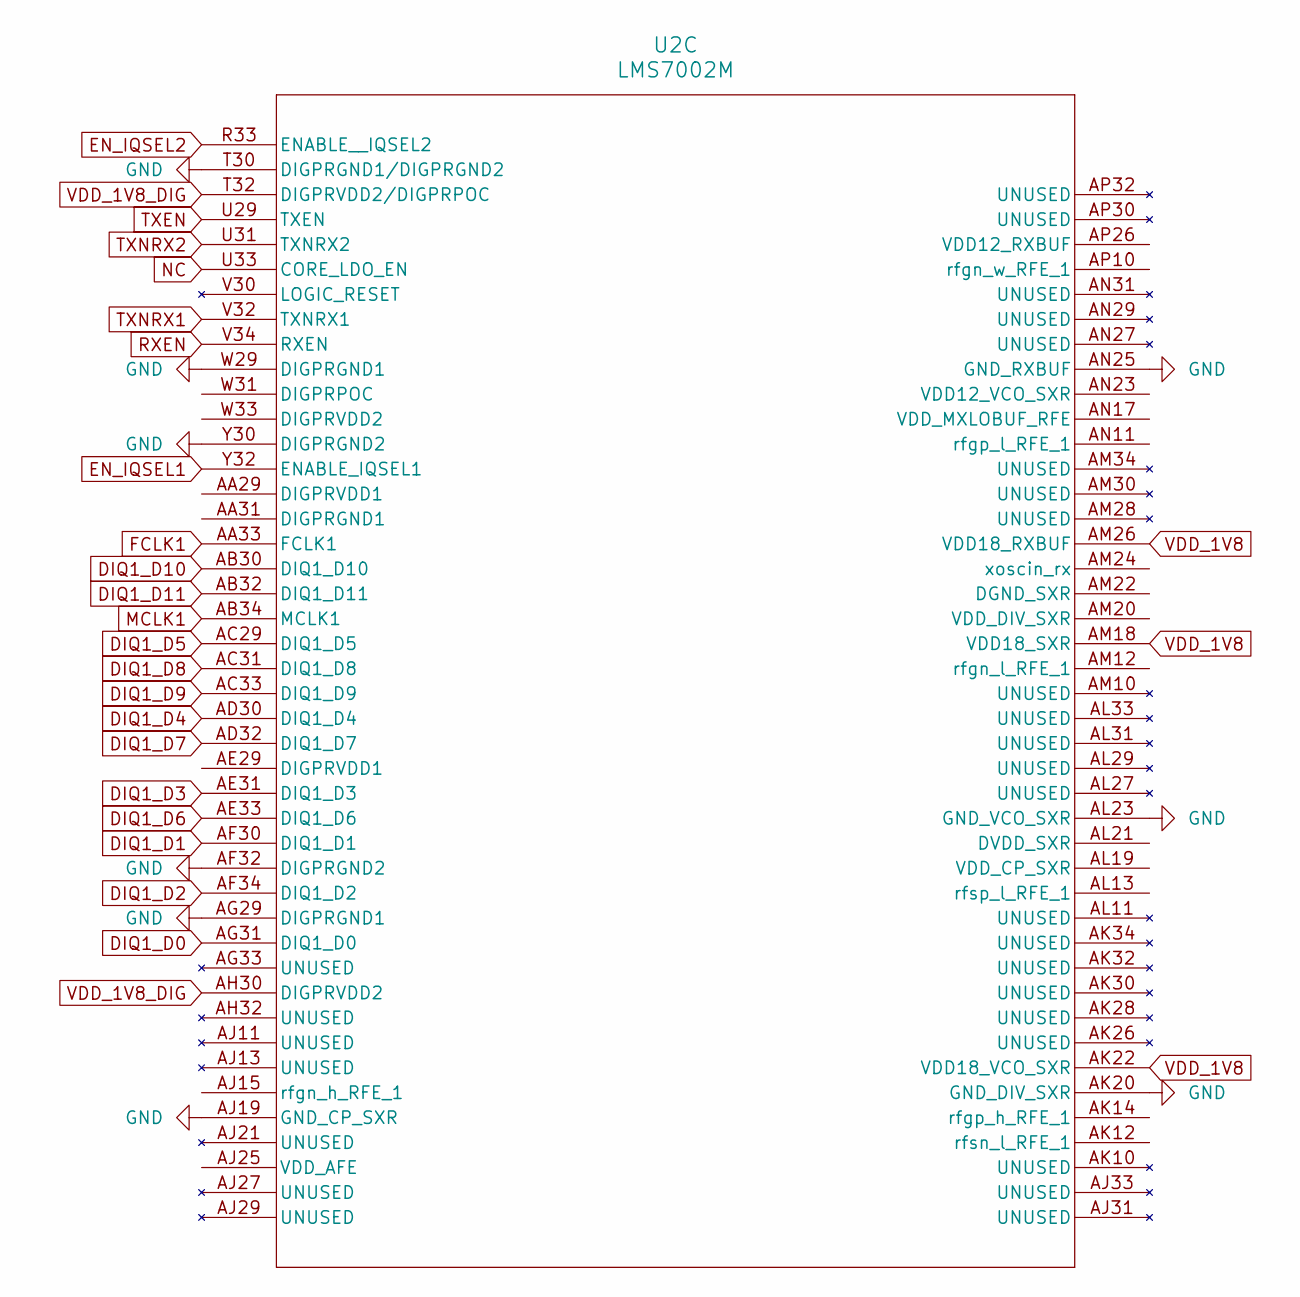
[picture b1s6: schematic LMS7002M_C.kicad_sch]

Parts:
U2: LMS7002M; AQFN261_11P5X11P5_LIM

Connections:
DIQ1_D0: U2.AG31 (DIQ1_D0); also elsewhere on the board
DIQ1_D1: U2.AF30 (DIQ1_D1); also elsewhere on the board
DIQ1_D2: U2.AF34 (DIQ1_D2); also elsewhere on the board
DIQ1_D3: U2.AE31 (DIQ1_D3); also elsewhere on the board
DIQ1_D4: U2.AD30 (DIQ1_D4); also elsewhere on the board
DIQ1_D5: U2.AC29 (DIQ1_D5); also elsewhere on the board
DIQ1_D6: U2.AE33 (DIQ1_D6); also elsewhere on the board
DIQ1_D7: U2.AD32 (DIQ1_D7); also elsewhere on the board
DIQ1_D8: U2.AC31 (DIQ1_D8); also elsewhere on the board
DIQ1_D9: U2.AC33 (DIQ1_D9); also elsewhere on the board
DIQ1_D11: U2.AB32 (DIQ1_D11); also elsewhere on the board
EN_IQSEL1: U2.Y32 (ENABLE_IQSEL1); also elsewhere on the board
EN_IQSEL2: U2.R33 (ENABLE__IQSEL2); also elsewhere on the board
FCLK1: U2.AA33 (FCLK1); also elsewhere on the board
GND: U2.AF32 (DIGPRGND2), U2.AG29 (DIGPRGND1), U2.AJ19 (GND_CP_SXR), U2.AK20 (GND_DIV_SXR), U2.AL23 (GND_VCO_SXR), U2.AN25 (GND_RXBUF), U2.T30 (DIGPRGND1/DIGPRGND2), U2.W29 (DIGPRGND1), U2.Y30 (DIGPRGND2); also elsewhere on the board
MCLK1: U2.AB34 (MCLK1); also elsewhere on the board
NC: U2.U33 (CORE_LDO_EN)
RXEN: U2.V34 (RXEN); also elsewhere on the board
TXEN: U2.U29 (TXEN); also elsewhere on the board
TXNRX1: U2.V32 (TXNRX1); also elsewhere on the board
TXNRX2: U2.U31 (TXNRX2); also elsewhere on the board
VDD_1V8: U2.AK22 (VDD18_VCO_SXR), U2.AM18 (VDD18_SXR), U2.AM26 (VDD18_RXBUF); also elsewhere on the board
VDD_1V8_DIG: U2.AH30 (DIGPRVDD2), U2.T32 (DIGPRVDD2/DIGPRPOC); also elsewhere on the board

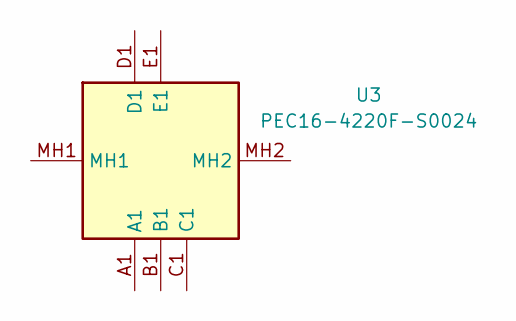
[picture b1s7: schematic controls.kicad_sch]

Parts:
U3: PEC16-4220F-S0024; PEC164120FS0012; Mouser Part Number 652-PEC16-4220FS0024
